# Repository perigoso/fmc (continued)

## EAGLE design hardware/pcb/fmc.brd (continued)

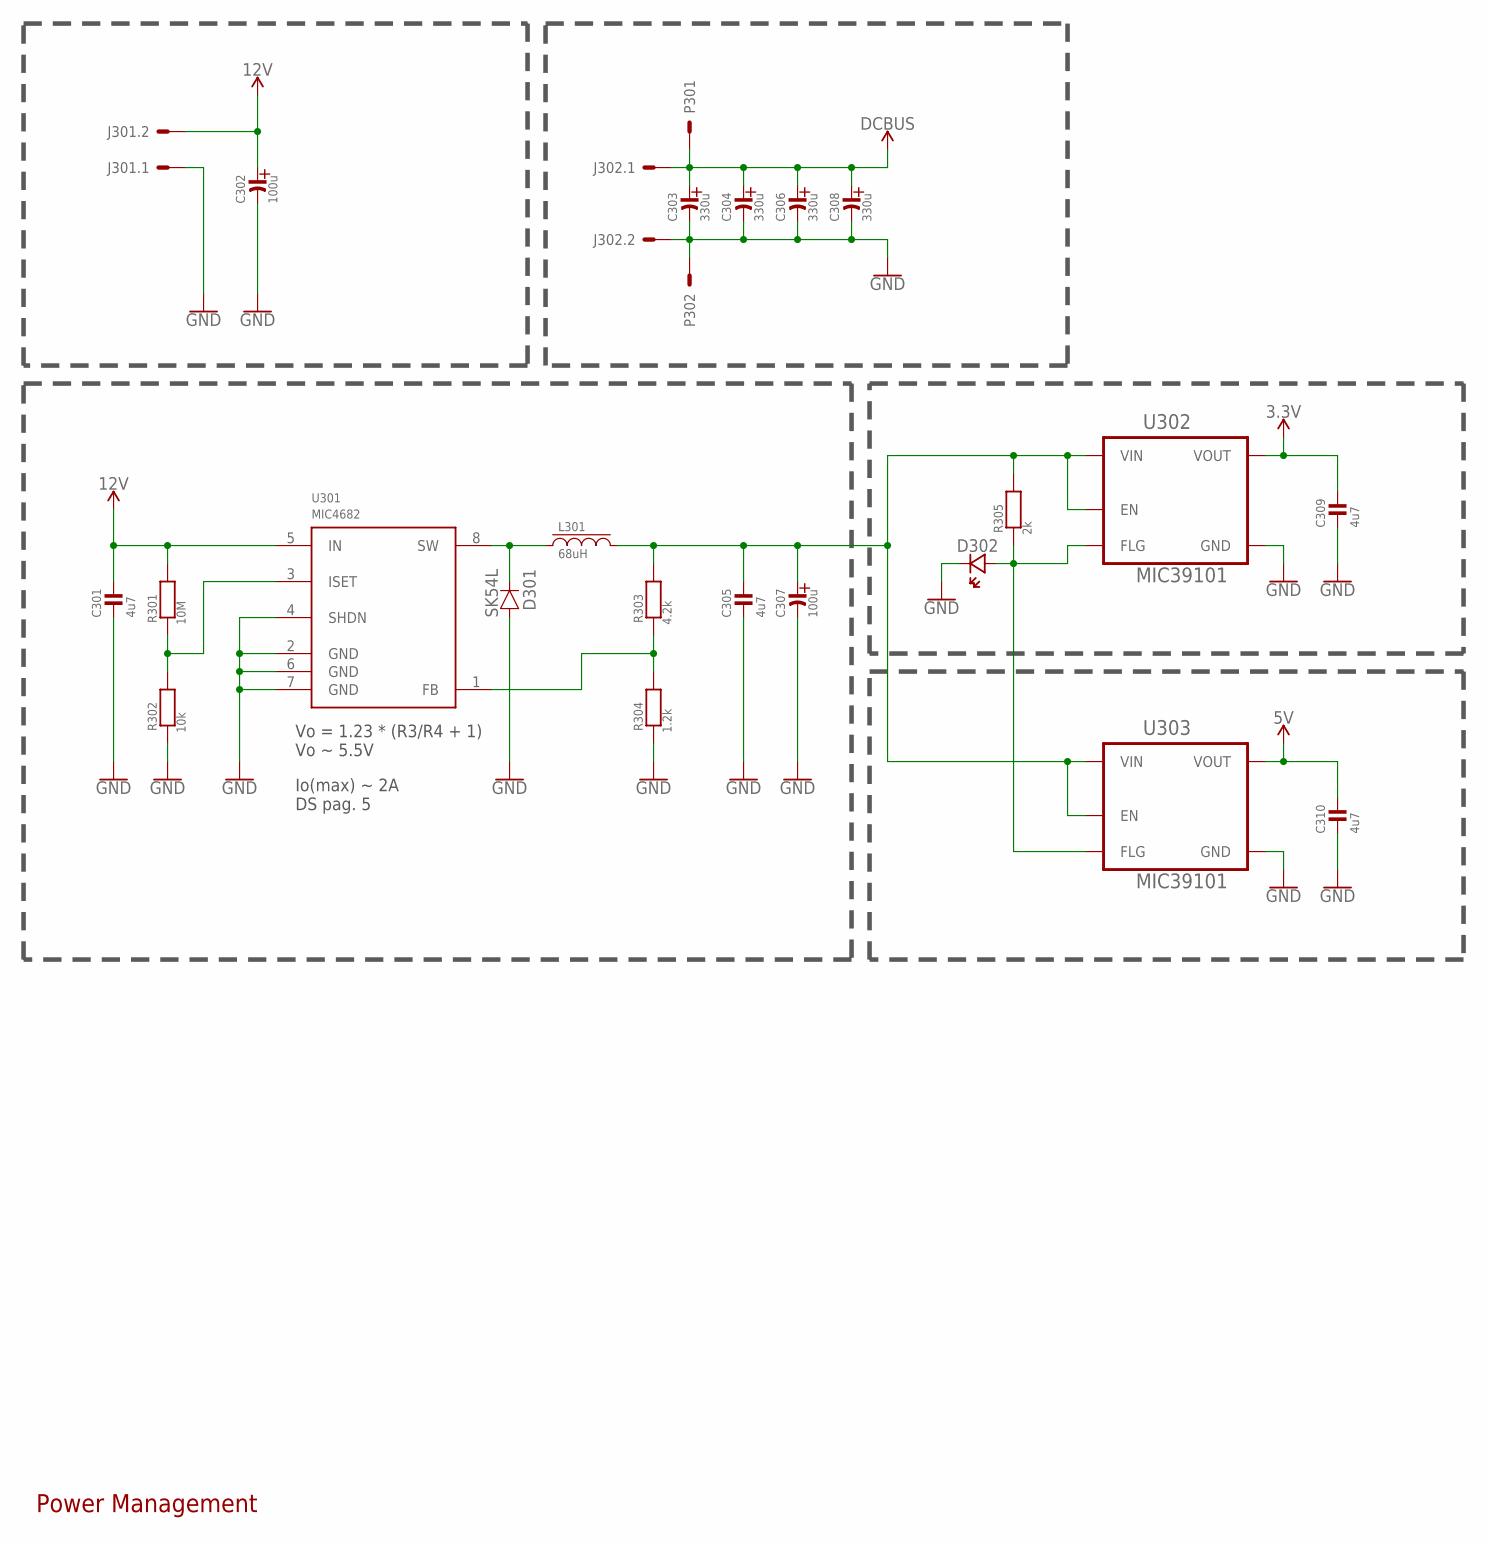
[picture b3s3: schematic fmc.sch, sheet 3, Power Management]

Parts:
C301, C305, C309, C310: 4u7; 0603_WAVE
C302, C307: 100u; PANASONIC_D
C303, C304, C306, C308: 330u; PANASONIC_G
D301: SK54L; DO214AA
D302: LED0603; CHIPLED_0603
J301, J302: 2P-6.35P
L301: 68uH; CDRH104R
P301, P302: POWPAD; TH-HP
R301: 10M; 0603_WAVE
R302: 10k; 0603_WAVE
R303: 4.2k; 0603_WAVE
R304: 1.2k; 0603_WAVE
R305: 2k; 0603_WAVE
U301: MIC4682; SOIC8
U302, U303: MIC39101; SOIC8

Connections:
3.3V: C309.P$1, U302.3 (VOUT); also elsewhere on the board
5V: C310.P$1, U303.3 (VOUT); also elsewhere on the board
12V: C301.P$1, C302.+ (AN), J301.2, R301.P$2, U301.5 (IN); also elsewhere on the board
DCBUS: C303.+ (AN), C304.+ (AN), C306.+ (AN), C308.+ (AN), J302.1, P301.H1, P301.H2, P301.H3, P301.H4, P301.H5, P301.H6, P301.H7, P301.H8, P301.H9, P301.H10, P301.H11, P301.H12, P301.PAD; also elsewhere on the board
GND: C301.P$2, C302.- (CA), C303.- (CA), C304.- (CA), C305.P$2, C306.- (CA), C307.- (CA), C308.- (CA), C309.P$2, C310.P$2, D301.A, D302.C (CA), J301.1, J302.2, P302.H1, P302.H2, P302.H3, P302.H4, P302.H5, P302.H6, P302.H7, P302.H8, P302.H9, P302.H10, P302.H11, P302.H12, P302.PAD, R302.P$1, R304.P$1, U301.2 (GND), U301.4 (SHDN), U301.6 (GND), U301.7 (GND), U302.5 (GND), U302.6 (GND), U302.7 (GND), U302.8 (GND), U303.5 (GND), U303.6 (GND), U303.7 (GND), U303.8 (GND); also elsewhere on the board
unnamed: C305.P$1, C307.+ (AN), L301.2, R303.P$2, R305.P$2, U302.1 (EN), U302.2 (VIN), U303.1 (EN), U303.2 (VIN)
unnamed: D301.C, L301.1, U301.8 (SW)
unnamed: R303.P$1, R304.P$2, U301.1 (FB)
unnamed: R301.P$1, R302.P$2, U301.3 (ISET)
unnamed: D302.A (AN), R305.P$1, U302.4 (FLG), U303.4 (FLG)

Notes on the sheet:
Power Management
Vo = 1.23 * (R3/R4 + 1) Vo ~ 5.5V
Io(max) ~ 2A DS pag. 5

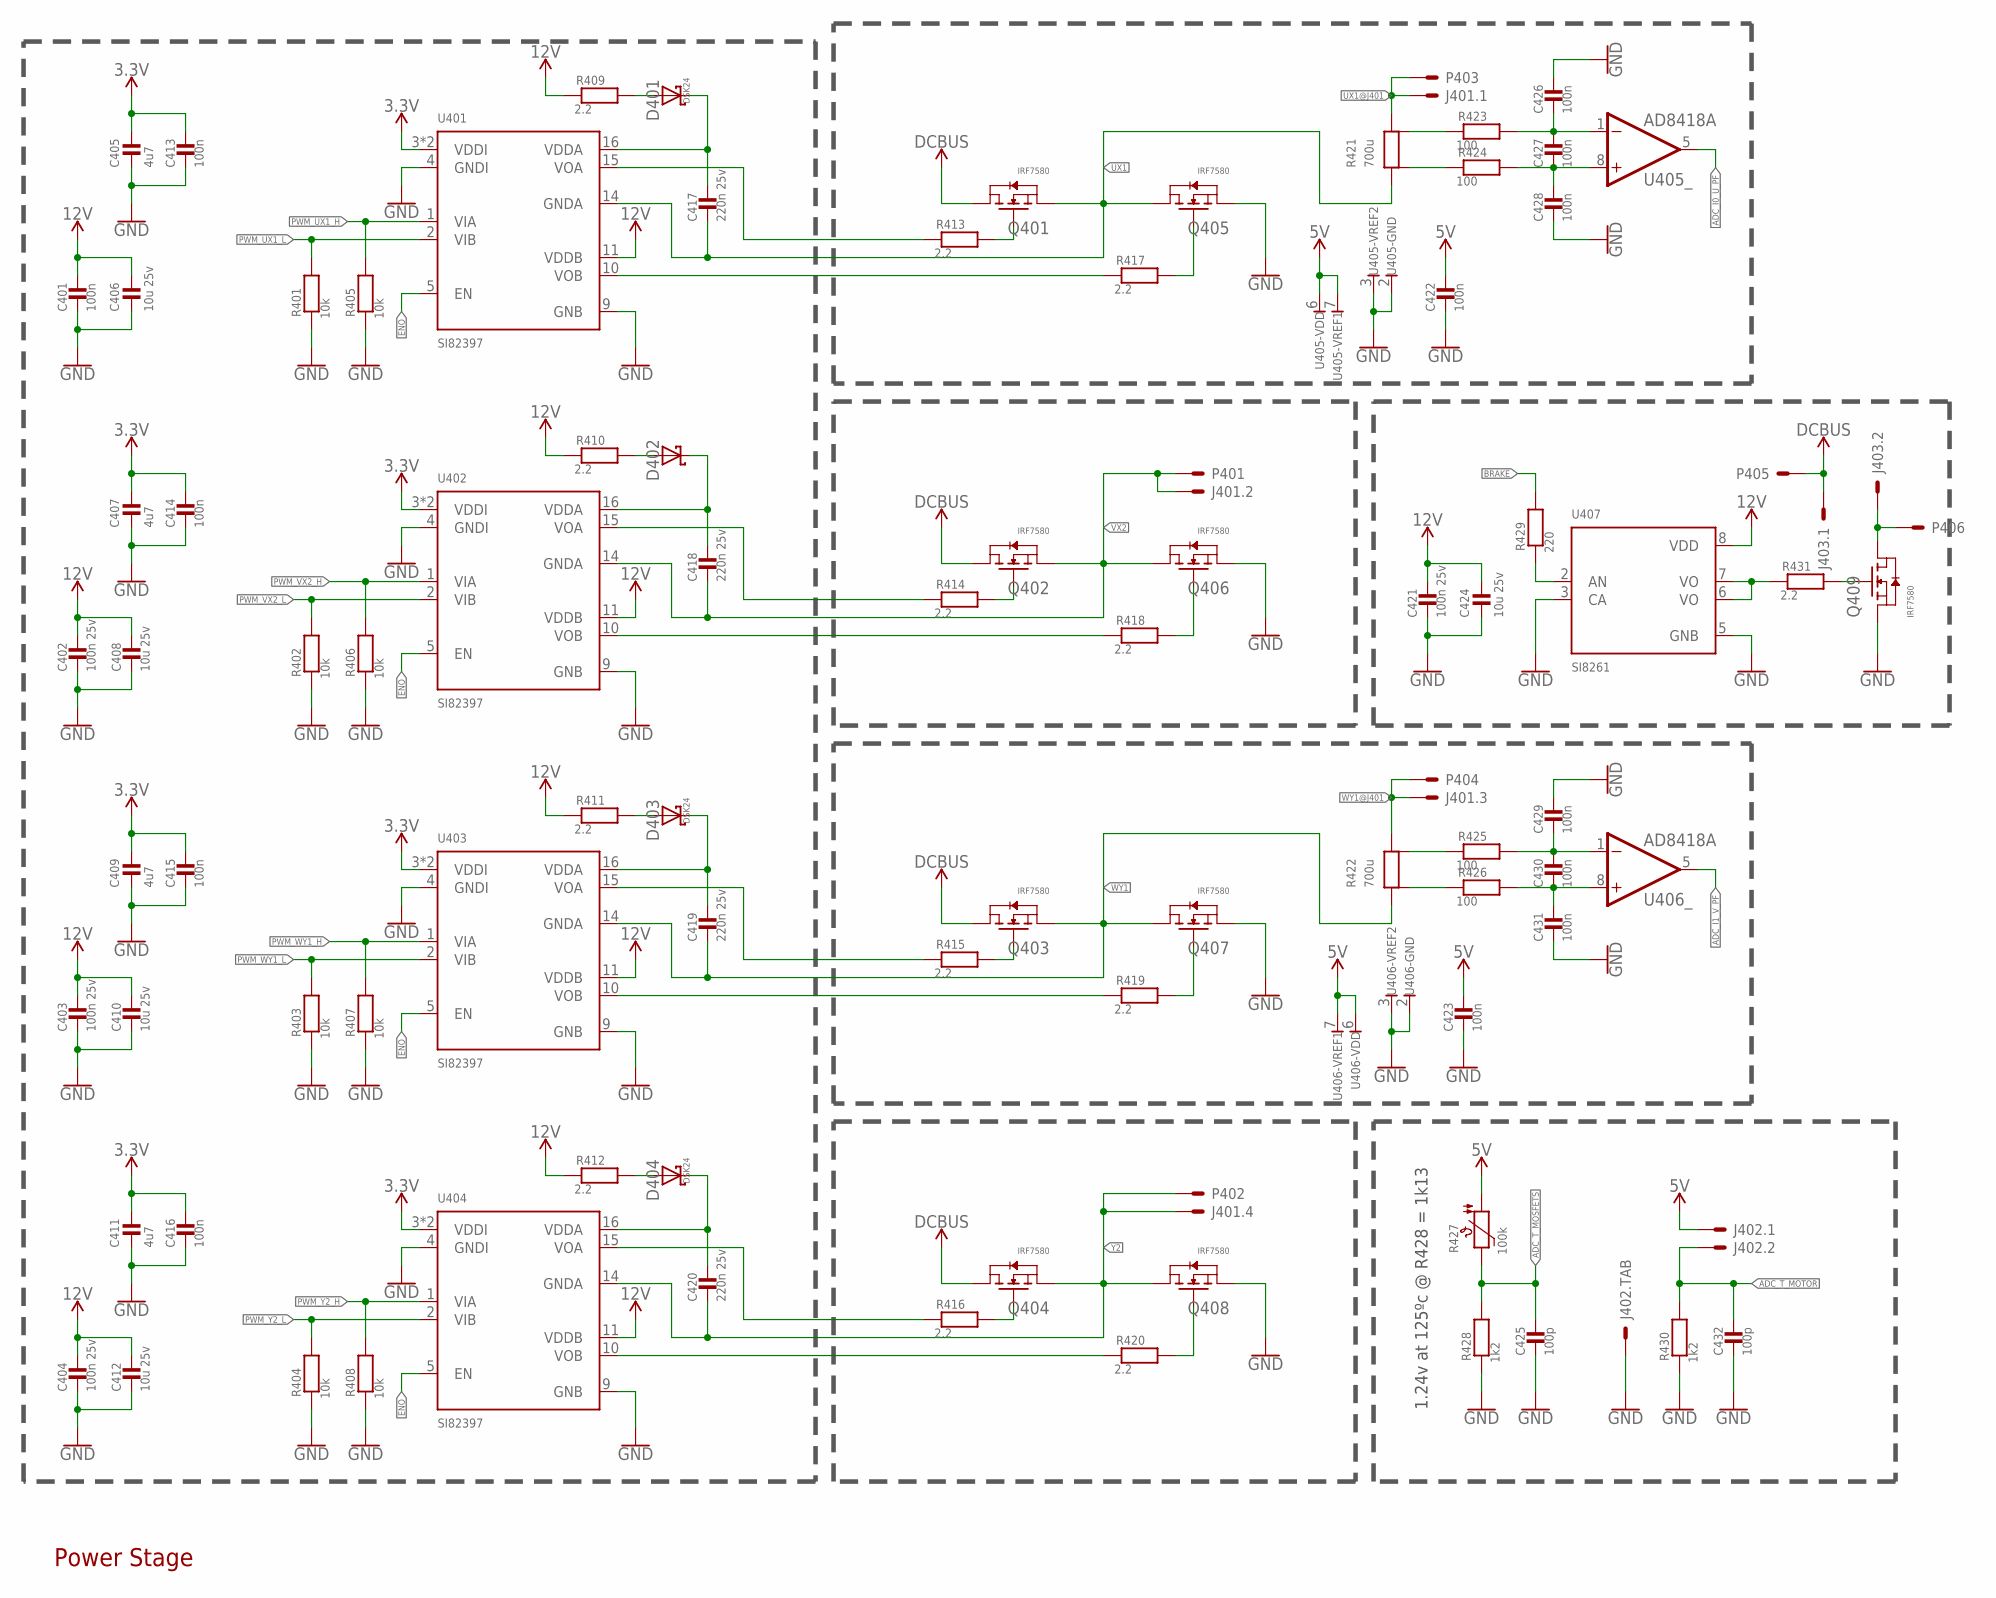
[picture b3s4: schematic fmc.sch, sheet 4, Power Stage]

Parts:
C401, C413, C414, C415, C416, C422, C423, C426, C427, C428, C429, C430, C431: 100n; 0603_WAVE
C402, C403, C404, C421: 100n 25v; 0603_WAVE
C405, C407, C409, C411: 4u7; 0603_WAVE
C406, C408, C410, C412, C424: 10u 25v; 0603_WAVE
C417, C418, C419, C420: 220n 25v; 0603_WAVE
C425, C432: 100p; 0603_WAVE
D401, D402, D403, D404: DSK24; SOD-123
J401: 4P-6.35P
J402: SH-2; SM02B-SSR-H-TB
J403: 2P-6.35P
P401, P402, P403, P404, P405, P406: POWPAD; TH-HP
Q401, Q402, Q403, Q404, Q405, Q406, Q407, Q408, Q409: IRF7580; DIRECTFET-ME
R401, R402, R403, R404, R405, R406, R407, R408: 10k; 0603_WAVE
R409, R410, R411, R412, R413, R414, R415, R416, R417, R418, R419, R420, R431: 2.2; 0603_WAVE
R421, R422: 700u; 3920
R423, R424, R425, R426: 100; 0603_WAVE
R427: 100k; 0603_WAVE
R428, R430: 1k2; 0603_WAVE
R429: 220; 0603_WAVE
U401, U402, U403, U404: SI82397; SOIC-16-WB
U405, U406: AD8418A; MSOP-8
U407: SI8261; SOIC_8

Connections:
3.3V: C405.P$1, C407.P$1, C409.P$1, C411.P$1, C413.P$1, C414.P$1, C415.P$1, C416.P$1, U401.3 (VDDI), U401.8 (VDDI), U402.3 (VDDI), U402.8 (VDDI), U403.3 (VDDI), U403.8 (VDDI), U404.3 (VDDI), U404.8 (VDDI); also elsewhere on the board
5V: C422.P$1, C423.P$1, J402.1, R427.P$2, U405.6, U405.7, U406.6, U406.7; also elsewhere on the board
12V: C401.P$1, C402.P$1, C403.P$1, C404.P$1, C406.P$1, C408.P$1, C410.P$1, C412.P$1, C421.P$1, C424.P$1, R409.P$1, R410.P$1, R411.P$1, R412.P$1, U401.11 (VDDB), U402.11 (VDDB), U403.11 (VDDB), U404.11 (VDDB), U407.8 (VDD); also elsewhere on the board
ADC_I0_U_PF: U405.5 (O); also elsewhere on the board
ADC_I1_V_PF: U406.5 (O); also elsewhere on the board
ADC_T_MOSFETS: C425.P$1, R427.P$1, R428.P$2; also elsewhere on the board
ADC_T_MOTOR: C432.P$1, J402.2, R430.P$2; also elsewhere on the board
BRAKE: R429.P$2; also elsewhere on the board
DCBUS: J403.1, P405.H1, P405.H2, P405.H3, P405.H4, P405.H5, P405.H6, P405.H7, P405.H8, P405.H9, P405.H10, P405.H11, P405.H12, P405.PAD, Q401.D1, Q401.D2 (D1), Q401.D3 (D1), Q401.D4 (D1), Q402.D1, Q402.D2 (D1), Q402.D3 (D1), Q402.D4 (D1), Q403.D1, Q403.D2 (D1), Q403.D3 (D1), Q403.D4 (D1), Q404.D1, Q404.D2 (D1), Q404.D3 (D1), Q404.D4 (D1); also elsewhere on the board
ENO: U401.5 (EN), U402.5 (EN), U403.5 (EN), U404.5 (EN); also elsewhere on the board
GND: C401.P$2, C402.P$2, C403.P$2, C404.P$2, C405.P$2, C406.P$2, C407.P$2, C408.P$2, C409.P$2, C410.P$2, C411.P$2, C412.P$2, C413.P$2, C414.P$2, C415.P$2, C416.P$2, C421.P$2, C422.P$2, C423.P$2, C424.P$2, C425.P$2, C426.P$1, C428.P$2, C429.P$1, C431.P$2, C432.P$2, J402.FIT@1, J402.FIT@2, Q405.S1, Q405.S2 (S1), Q405.S3 (S1), Q405.S4 (S1), Q405.S5 (S1), Q406.S1, Q406.S2 (S1), Q406.S3 (S1), Q406.S4 (S1), Q406.S5 (S1), Q407.S1, Q407.S2 (S1), Q407.S3 (S1), Q407.S4 (S1), Q407.S5 (S1), Q408.S1, Q408.S2 (S1), Q408.S3 (S1), Q408.S4 (S1), Q408.S5 (S1), Q409.S1, Q409.S2 (S1), Q409.S3 (S1), Q409.S4 (S1), Q409.S5 (S1), R401.P$1, R402.P$1, R403.P$1, R404.P$1, R405.P$1, R406.P$1, R407.P$1, R408.P$1, R428.P$1, R430.P$1, U401.4 (GNDI), U401.9 (GNB), U402.4 (GNDI), U402.9 (GNB), U403.4 (GNDI), U403.9 (GNB), U404.4 (GNDI), U404.9 (GNB), U405.2, U405.3, U406.2, U406.3, U407.3 (CA), U407.5 (GNB); also elsewhere on the board
unnamed: R413.P$1, U401.15 (VOA)
unnamed: Q405.G (G1), R417.P$2
unnamed: R421.SENSE+, R424.P$1
unnamed: C417.P$1, D401.C, U401.16 (VDDA)
unnamed: R414.P$1, U402.15 (VOA)
unnamed: Q406.G (G1), R418.P$2
unnamed: R421.SENSE-, R423.P$1
unnamed: C418.P$1, D402.C, U402.16 (VDDA)
unnamed: R415.P$1, U403.15 (VOA)
unnamed: Q407.G (G1), R419.P$2
unnamed: C426.P$2, C427.P$1, R423.P$2, U405.1 (IN-)
unnamed: C419.P$1, D403.C, U403.16 (VDDA)
unnamed: R416.P$1, U404.15 (VOA)
unnamed: Q408.G (G1), R420.P$2
unnamed: C427.P$2, C428.P$1, R424.P$2, U405.8 (IN+)
unnamed: C420.P$1, D404.C, U404.16 (VDDA)
unnamed: Q403.G (G1), R415.P$2
unnamed: Q401.G (G1), R413.P$2
unnamed: Q402.G (G1), R414.P$2
unnamed: Q404.G (G1), R416.P$2
unnamed: R417.P$1, U401.10 (VOB)
unnamed: R418.P$1, U402.10 (VOB)
unnamed: R419.P$1, U403.10 (VOB)
unnamed: R420.P$1, U404.10 (VOB)
unnamed: D404.A, R412.P$2
unnamed: D403.A, R411.P$2
unnamed: D402.A, R410.P$2
unnamed: D401.A, R409.P$2
unnamed: R422.SENSE-, R425.P$1
unnamed: R422.SENSE+, R426.P$1
unnamed: C430.P$2, C431.P$1, R426.P$2, U406.8 (IN+)
unnamed: C429.P$2, C430.P$1, R425.P$2, U406.1 (IN-)
unnamed: R429.P$1, U407.2 (AN)
unnamed: Q409.G (G1), R431.P$2
unnamed: R431.P$1, U407.6 (VO), U407.7 (VO)
unnamed: J403.2, P406.H1, P406.H2, P406.H3, P406.H4, P406.H5, P406.H6, P406.H7, P406.H8, P406.H9, P406.H10, P406.H11, P406.H12, P406.PAD, Q409.D1, Q409.D2 (D1), Q409.D3 (D1), Q409.D4 (D1)
PWM_UX1_H: R405.P$2, U401.1 (VIA); also elsewhere on the board
PWM_UX1_L: R401.P$2, U401.2 (VIB); also elsewhere on the board
PWM_VX2_H: R406.P$2, U402.1 (VIA); also elsewhere on the board
PWM_VX2_L: R402.P$2, U402.2 (VIB); also elsewhere on the board
PWM_WY1_H: R407.P$2, U403.1 (VIA); also elsewhere on the board
PWM_WY1_L: R403.P$2, U403.2 (VIB); also elsewhere on the board
PWM_Y2_H: R408.P$2, U404.1 (VIA); also elsewhere on the board
PWM_Y2_L: R404.P$2, U404.2 (VIB); also elsewhere on the board
UX1: C417.P$2, Q401.S1, Q401.S2 (S1), Q401.S3 (S1), Q401.S4 (S1), Q401.S5 (S1), Q405.D1, Q405.D2 (D1), Q405.D3 (D1), Q405.D4 (D1), R421.1, R421.2, U401.14 (GNDA)
UX1@J401: J401.1, P403.H1, P403.H2, P403.H3, P403.H4, P403.H5, P403.H6, P403.H7, P403.H8, P403.H9, P403.H10, P403.H11, P403.H12, P403.PAD, R421.3, R421.4
VX2: C418.P$2, J401.2, P401.H1, P401.H2, P401.H3, P401.H4, P401.H5, P401.H6, P401.H7, P401.H8, P401.H9, P401.H10, P401.H11, P401.H12, P401.PAD, Q402.S1, Q402.S2 (S1), Q402.S3 (S1), Q402.S4 (S1), Q402.S5 (S1), Q406.D1, Q406.D2 (D1), Q406.D3 (D1), Q406.D4 (D1), U402.14 (GNDA)
WY1: C419.P$2, Q403.S1, Q403.S2 (S1), Q403.S3 (S1), Q403.S4 (S1), Q403.S5 (S1), Q407.D1, Q407.D2 (D1), Q407.D3 (D1), Q407.D4 (D1), R422.1, R422.2, U403.14 (GNDA)
WY1@J401: J401.3, P404.H1, P404.H2, P404.H3, P404.H4, P404.H5, P404.H6, P404.H7, P404.H8, P404.H9, P404.H10, P404.H11, P404.H12, P404.PAD, R422.3, R422.4
Y2: C420.P$2, J401.4, P402.H1, P402.H2, P402.H3, P402.H4, P402.H5, P402.H6, P402.H7, P402.H8, P402.H9, P402.H10, P402.H11, P402.H12, P402.PAD, Q404.S1, Q404.S2 (S1), Q404.S3 (S1), Q404.S4 (S1), Q404.S5 (S1), Q408.D1, Q408.D2 (D1), Q408.D3 (D1), Q408.D4 (D1), U404.14 (GNDA)

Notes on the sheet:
Power Stage
1.24v at 125ºc @ R428 = 1k13

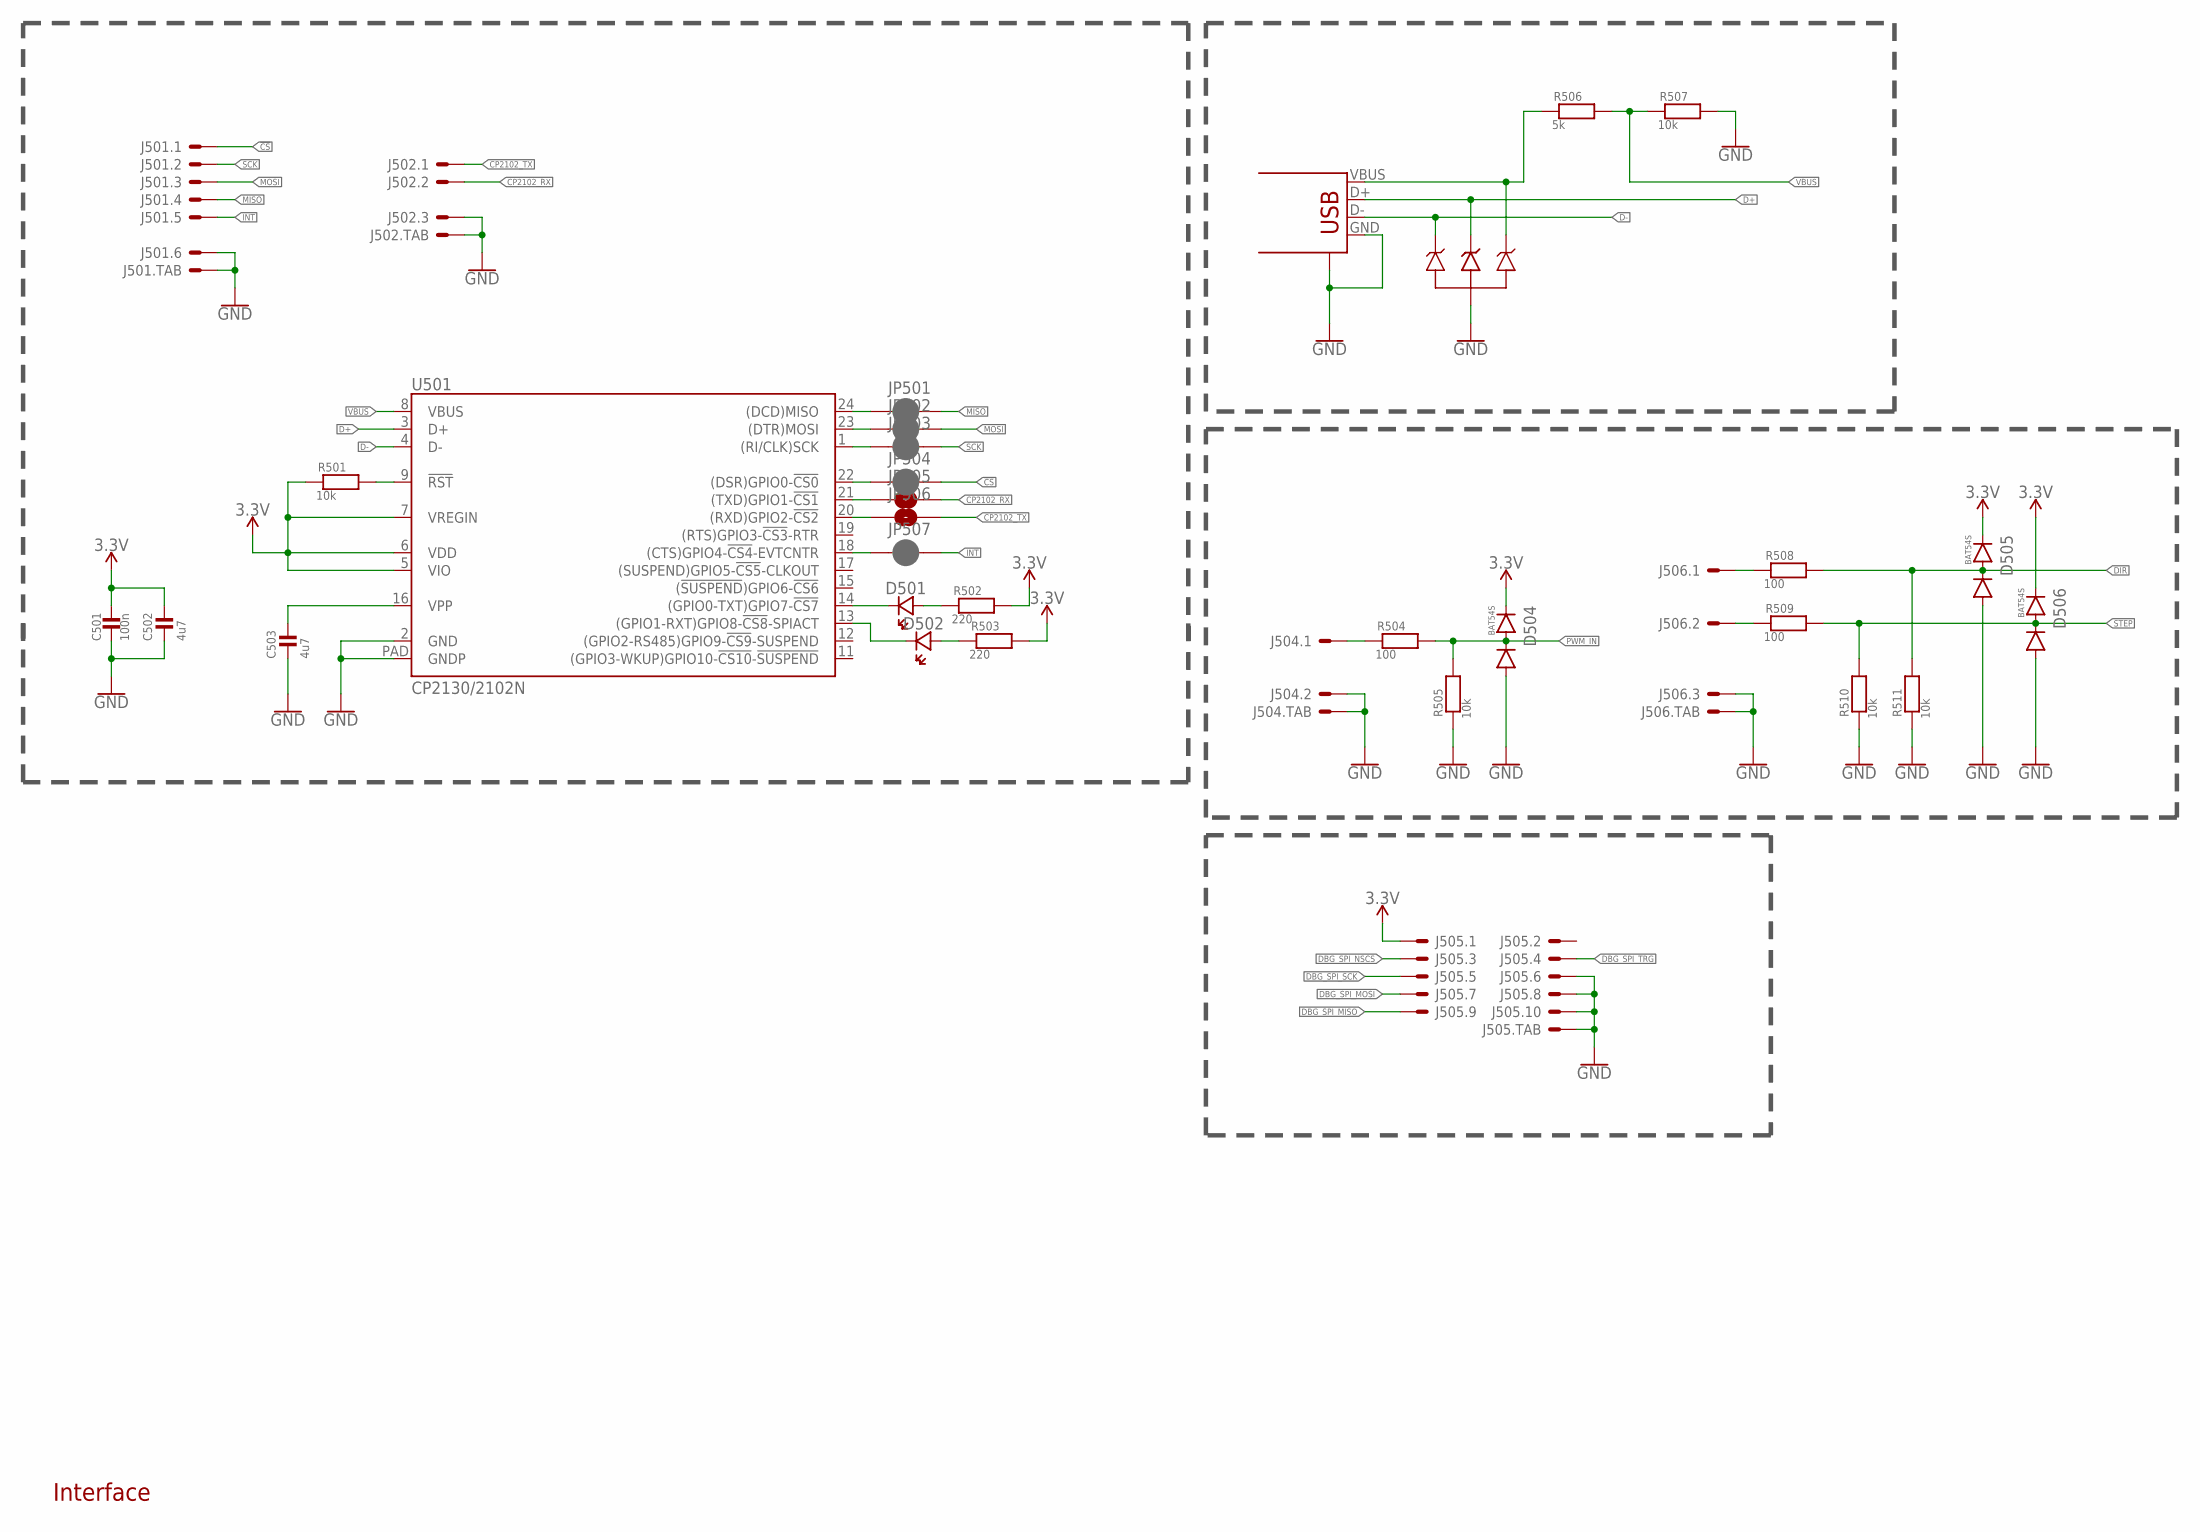
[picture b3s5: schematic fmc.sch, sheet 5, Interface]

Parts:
C501: 100n; 0603_WAVE
C502, C503: 4u7; 0603_WAVE
D501, D502: LED0603; CHIPLED_0603
D503: SP0503BAHT; SOT143
D504, D505, D506: BAT54S; SOT-23-3
J501: SH-6; SM06B-SSR-H-TB
J502, J506: SH-3; SM03B-SSR-H-TB
J503: USB-SHIELD; USB-M-S1
J504: SH-2; SM02B-SSR-H-TB
J505: F20F-10DP-1V
JP501, JP502, JP503, JP504, JP507: JUMPER-SMT_2_NC_PASTE_SILK; SMT-JUMPER_2_NC_PASTE_SILK
JP505, JP506: JUMPER-SMT_2_NO_SILK; SMT-JUMPER_2_NO_SILK
R501, R505, R507, R510, R511: 10k; 0603_WAVE
R502, R503: 220; 0603_WAVE
R504, R508, R509: 100; 0603_WAVE
R506: 5k; 0603_WAVE
U501: CP2130/2102N; QFN24

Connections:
3.3V: C501.P$1, C502.P$1, D504.P$2 (2), D505.P$2 (2), D506.P$2 (2), J505.1, R501.P$1, R502.P$2, R503.P$2, U501.5 (VIO), U501.6 (VDD), U501.7 (VREGIN); also elsewhere on the board
!CS: J501.1, JP504.2; also elsewhere on the board
CP2102_RX: J502.2, JP505.2; also elsewhere on the board
CP2102_TX: J502.1, JP506.2; also elsewhere on the board
D+: D503.3, J503.D+, U501.3 (D+)
D-: D503.2, J503.D-, U501.4 (D-)
DBG_SPI_MISO: J505.9; also elsewhere on the board
DBG_SPI_MOSI: J505.7; also elsewhere on the board
DBG_SPI_NSCS: J505.3; also elsewhere on the board
DBG_SPI_SCK: J505.5; also elsewhere on the board
DBG_SPI_TRG: J505.4; also elsewhere on the board
DIR: D505.P$3 (3), R508.P$2, R511.P$2; also elsewhere on the board
DIR@J: J506.1, R508.P$1
GND: C501.P$2, C502.P$2, C503.P$2, D503.1, D504.P$1 (1), D505.P$1 (1), D506.P$1 (1), J501.6, J501.FIT@1, J501.FIT@2, J502.3, J502.FIT@1, J502.FIT@2, J503.GND, J503.GND@1 (CASE), J503.GND@2 (CASE), J503.GND@3 (CASE), J503.GND@4 (CASE), J504.2, J504.FIT@1, J504.FIT@2, J505.6, J505.8, J505.10, J505.TAB1, J505.TAB2, J506.3, J506.FIT@1, J506.FIT@2, R505.P$1, R507.P$2, R510.P$1, R511.P$1, U501.2 (GND), U501.PAD (GNDP); also elsewhere on the board
INT: J501.5, JP507.2; also elsewhere on the board
MISO: J501.4, JP501.2; also elsewhere on the board
MOSI: J501.3, JP502.2; also elsewhere on the board
unnamed: D503.4, J503.VBUS, R506.P$1
unnamed: R501.P$2, U501.9 (!RST)
unnamed: C503.P$1, U501.16 (VPP)
unnamed: D501.C (CA), U501.14 ((GPIO0-TXT)GPIO7-!CS7)
unnamed: D502.C (CA), U501.13 ((GPIO1-RXT)GPIO8-!CS8!-SPIACT)
unnamed: D501.A (AN), R502.P$1
unnamed: D502.A (AN), R503.P$1
unnamed: JP506.1, U501.20 ((RXD)GPIO2-!CS2)
unnamed: JP505.1, U501.21 ((TXD)GPIO1-!CS1)
unnamed: JP507.1, U501.18 ((CTS)GPIO4-!CS4!-EVTCNTR)
unnamed: JP504.1, U501.22 ((DSR)GPIO0-!CS0)
unnamed: JP503.1, U501.1 ((RI/CLK)SCK)
unnamed: JP502.1, U501.23 ((DTR)MOSI)
unnamed: JP501.1, U501.24 ((DCD)MISO)
PWM_IN: D504.P$3 (3), R504.P$2, R505.P$2; also elsewhere on the board
PWM_IN@J: J504.1, R504.P$1
SCK: J501.2, JP503.2; also elsewhere on the board
STEP: D506.P$3 (3), R509.P$2, R510.P$2; also elsewhere on the board
STEP@J: J506.2, R509.P$1
VBUS: R506.P$2, R507.P$1, U501.8 (VBUS)

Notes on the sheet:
Interface

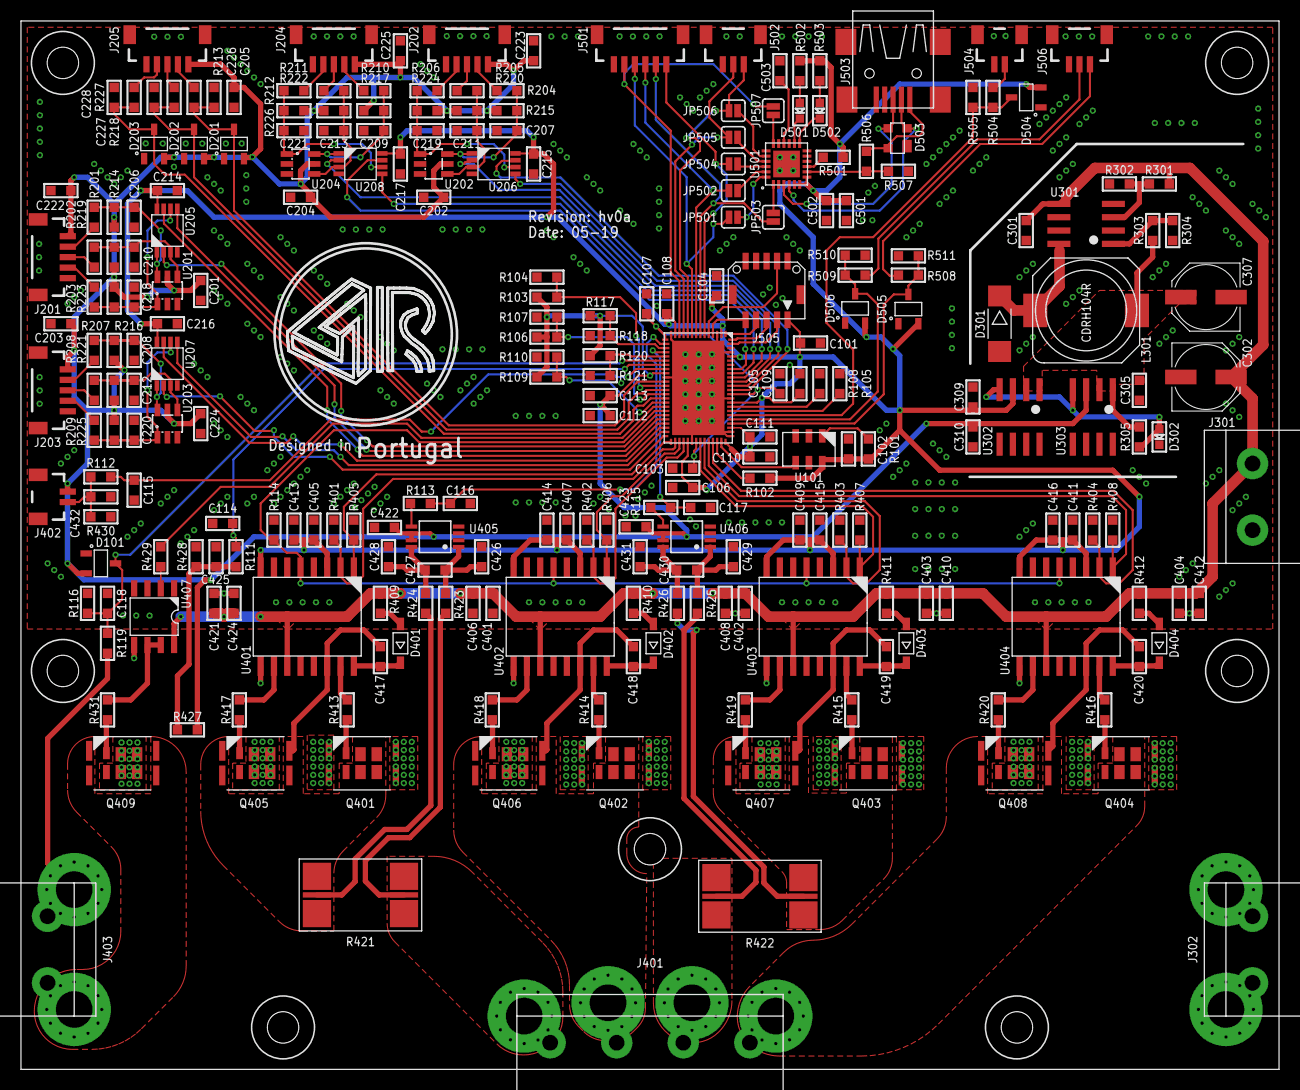
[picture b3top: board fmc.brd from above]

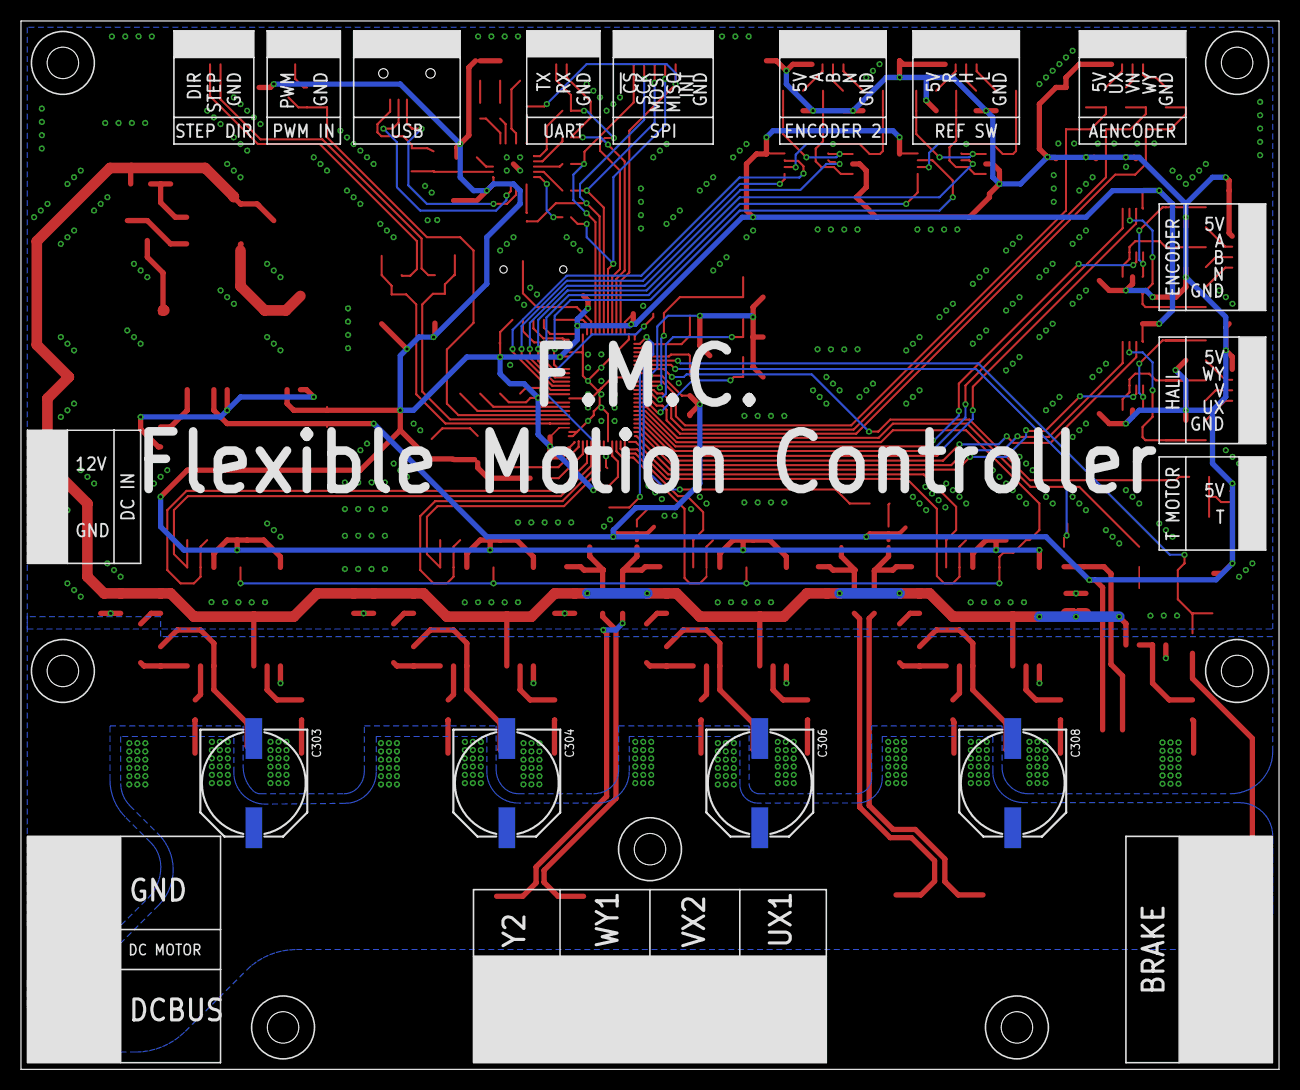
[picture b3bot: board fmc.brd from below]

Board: 2 copper layers, 120.0 x 100.0 mm, 265 parts (4 on the bottom side), 159 nets.

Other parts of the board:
U$1: RAFAEL_SILVA_10MM_CIRCLE

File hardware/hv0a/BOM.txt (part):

Partlist exported from /home/rafael/Development/ipl-motion-controller/hardware/hv0a/servo-ctrl.sch at 03/04/19 17:34

Qty Value                      Device                     Package                    Parts                                                                                                                                                                                                Description                                                                                        
1   1.2k                       RESISTOR0603               0603_WAVE                  R304                                                                                                                                                                                                 Resistors                                                                                          
23  100                        RESISTOR0603               0603_WAVE                  R111, R112, R113, R115, R201, R202, R203, R204, R205, R206, R207, R208, R209, R210, R211, R212, R213, R218, R227, R423, R424, R425, R426                                                             Resistors                                                                                          
1   100k                       NTC0603                    0603_WAVE                  R427                                                                                                                                                                                                 Resistors                                                                                          
12  100k                       RESISTOR0603               0603_WAVE                  R214, R215, R216, R217, R219, R220, R221, R222, R223, R224, R225, R226                                                                                                                               Resistors                                                                                          
33  100n                       MLCC0603                   0603_WAVE                  C101, C102, C103, C104, C105, C106, C107, C108, C109, C110, C112, C214, C215, C216, C217, C222, C223, C224, C225, C401, C413, C414, C415, C416, C422, C423, C426, C427, C428, C429, C430, C431, C501 KEMET’s X7R dielectric features a 125°C maximum                                                    
4   100n 25v                   MLCC0603                   0603_WAVE                  C402, C403, C404, C421                                                                                                                                                                               KEMET’s X7R dielectric features a 125°C maximum                                                    
22  100p                       MLCC0603                   0603_WAVE                  C114, C115, C116, C117, C118, C206, C207, C208, C209, C210, C211, C212, C213, C218, C219, C220, C221, C226, C227, C228, C425, C432                                                                   KEMET’s X7R dielectric features a 125°C maximum                                                    
2   100u                       CAPACITOR_ELD              PANASONIC_D                C302, C307                                                                                                                                                                                                                                                                                              
1   10M                        RESISTOR0603               0603_WAVE                  R301                                                                                                                                                                                                 Resistors                                                                                          
27  10k                        RESISTOR0603               0603_WAVE                  R101, R102, R103, R104, R105, R106, R107, R108, R109, R110, R114, R116, R117, R118, R120, R121, R302, R401, R402, R403, R404, R405, R406, R407, R408, R430, R501                                     Resistors                                                                                          
5   10u 25v                    MLCC0603                   0603_WAVE                  C406, C408, C410, C412, C424                                                                                                                                                                         KEMET’s X7R dielectric features a 125°C maximum                                                    
1   140k                       RESISTOR0603               0603_WAVE                  R119                                                                                                                                                                                                 Resistors                                                                                          
1   1k13                       RESISTOR0603               0603_WAVE                  R428                                                                                                                                                                                                 Resistors                                                                                          
13  2.2                        RESISTOR0603               0603_WAVE                  R409, R410, R411, R412, R413, R414, R415, R416, R417, R418, R419, R420, R431                                                                                                                         Resistors                                                                                          
3   220                        RESISTOR0603               0603_WAVE                  R429, R502, R503                                                                                                                                                                                     Resistors                                                                                          
4   220n 25v                   MLCC0603                   0603_WAVE                  C417, C418, C419, C420                                                                                                                                                                               KEMET’s X7R dielectric features a 125°C maximum                                                    
7   24k                        RESISTOR0603               0603_WAVE                  R504, R505, R506, R508, R509, R510, R511                                                                                                                                                             Resistors                                                                                          
3   2P-6.35P                   2P-6.35P                   2P-6.35P                   J301, J302, J403                                                                                                                                                                                                                                                                                        
1   2k                         RESISTOR0603               0603_WAVE                  R305                                                                                                                                                                                                 Resistors                                                                                          
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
